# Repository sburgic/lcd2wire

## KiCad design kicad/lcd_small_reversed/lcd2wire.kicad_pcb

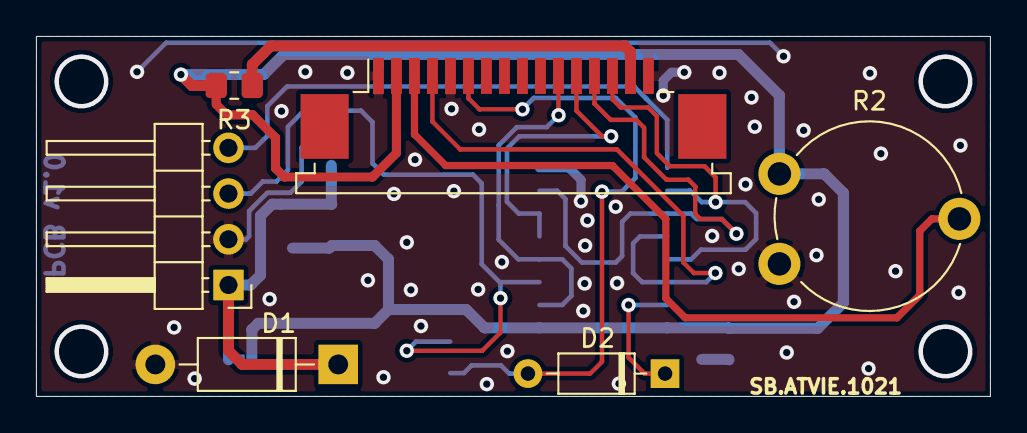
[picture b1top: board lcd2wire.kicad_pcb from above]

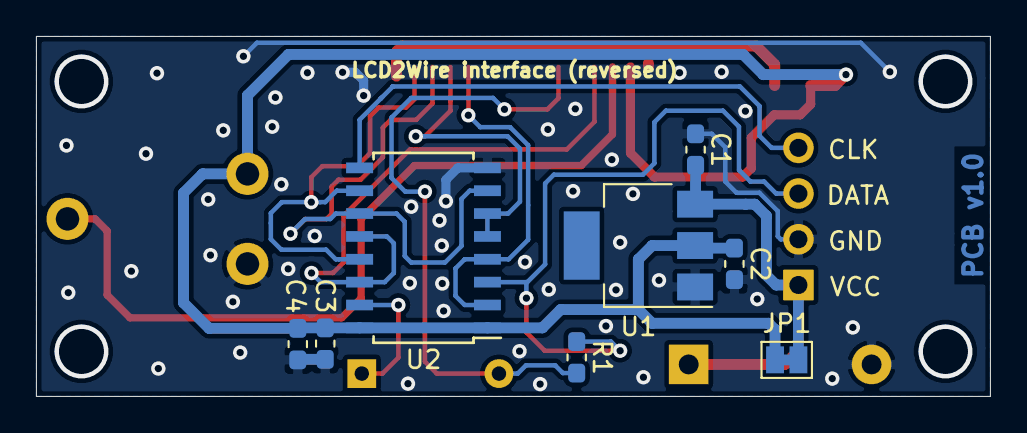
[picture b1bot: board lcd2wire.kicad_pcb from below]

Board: 2 copper layers, 53.0 x 20.0 mm, 14 parts (8 on the bottom side), 14 nets.

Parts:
C1, C2, C3: 100nF; C_0603_1608Metric_Pad1.05x0.95mm_HandSolder
C4: 1nF; C_0603_1608Metric_Pad1.05x0.95mm_HandSolder
D1: 1N4007; D_DO-41_SOD81_P10.16mm_Horizontal
D2: 1N4148; D_DO-35_SOD27_P7.62mm_Horizontal
J1: LCD2Wire; PinHeader_1x04_P2.54mm_Horizontal
J3: Conn_01x16; TE_1-84952-6_1x16-1MP_P1.0mm_Horizontal
JP1: Jumper; SolderJumper-2_P1.3mm_Bridged_Pad1.0x1.5mm
R1: 1K; R_0603_1608Metric_Pad1.05x0.95mm_HandSolder
R2: 5K; Potentiometer_Piher_PT-10-V10_Vertical
R3: *; R_0805_2012Metric_Pad1.20x1.40mm_HandSolder
U1: AZ1117-5.0; SOT-223
U2: 74LS174; SOIC-16W_5.3x10.2mm_P1.27mm

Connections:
+5V: C2.1, C3.1, C4.1, J3.2, JP1.2, R2.3, R3.1, U1.2, U2.1, U2.16
CLK: J1.4, U2.9
DATA: J1.3, R1.1, U2.3
GND: C1.2, C2.2, C3.2, C4.2, D1.2, J1.2, J3.1, J3.5, J3.16, R2.1, U1.1, U2.8
unnamed: D2.1, U2.15
unnamed: D2.2, J3.6, R1.2
unnamed: J3.3, R2.2
unnamed: J3.4, U2.12, U2.14
unnamed: J3.11, U2.2, U2.4
unnamed: J3.12, U2.5, U2.6
unnamed: J3.13, U2.7, U2.11
unnamed: J3.14, U2.10, U2.13
unnamed: J3.15, R3.2
VCC: C1.1, D1.1, J1.1, JP1.1, U1.3

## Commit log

2021-01-24 add pcb v1.0
2021-04-06 remove pcb folder
2021-04-21 add small lcd pcb v1.0
2021-10-05 Update text on lcd2wire large board
2021-10-30 Add LCD2Wire interface board small (reversed)
